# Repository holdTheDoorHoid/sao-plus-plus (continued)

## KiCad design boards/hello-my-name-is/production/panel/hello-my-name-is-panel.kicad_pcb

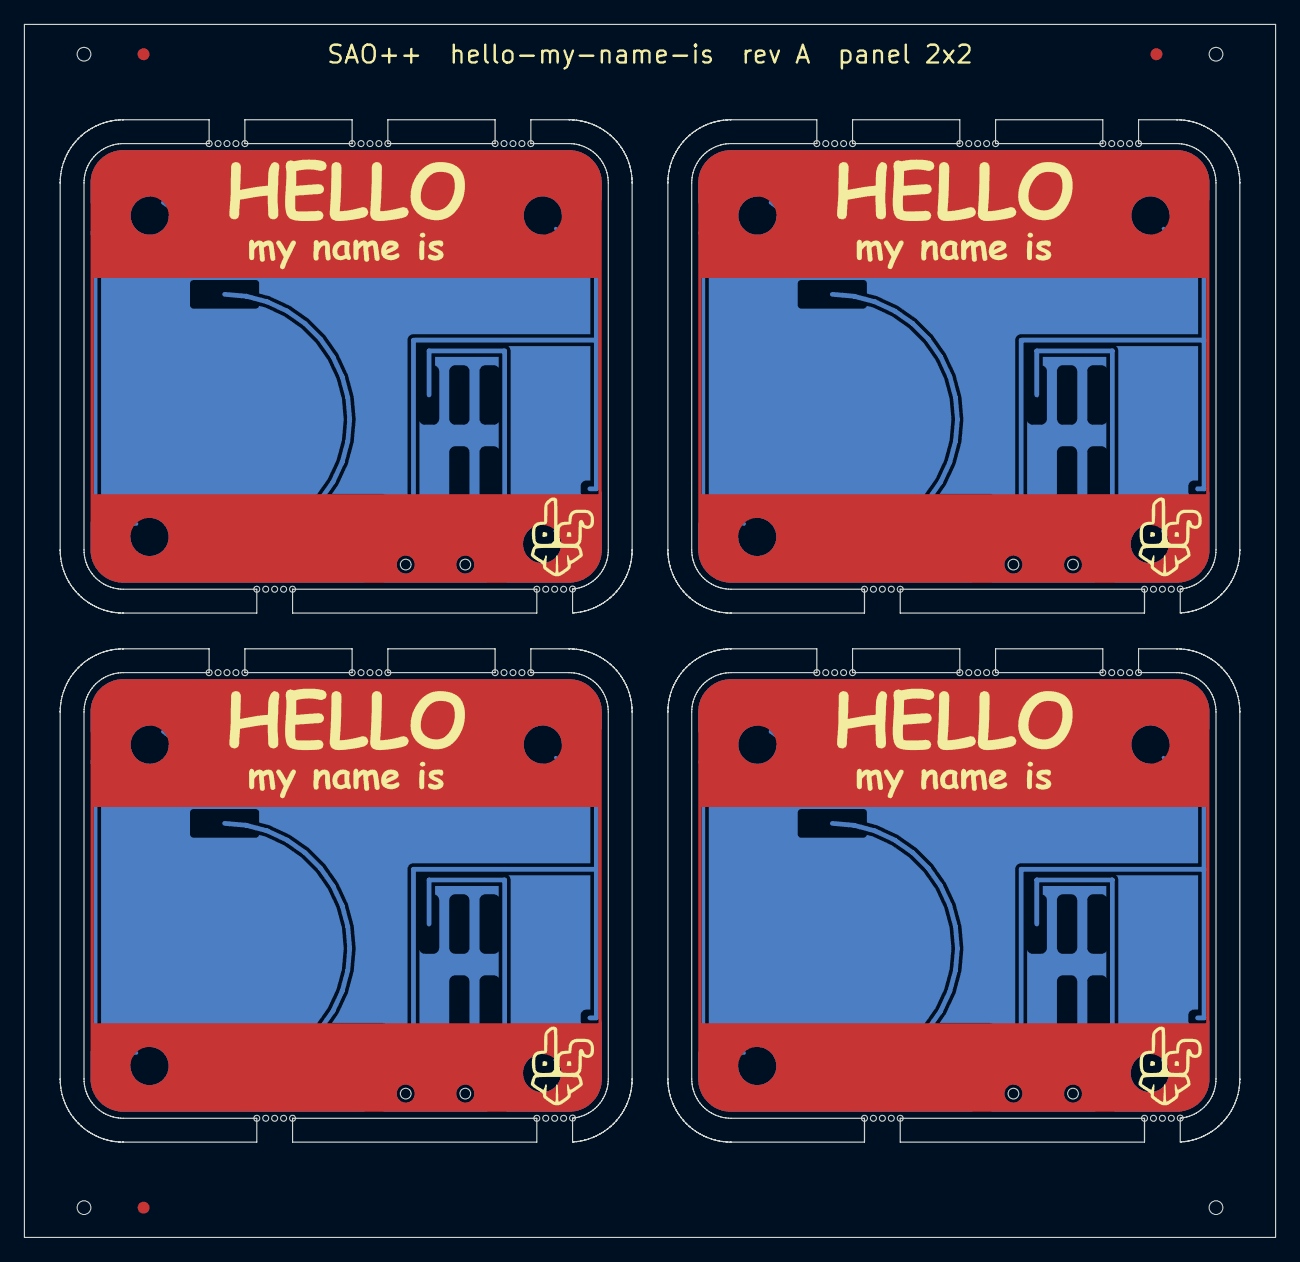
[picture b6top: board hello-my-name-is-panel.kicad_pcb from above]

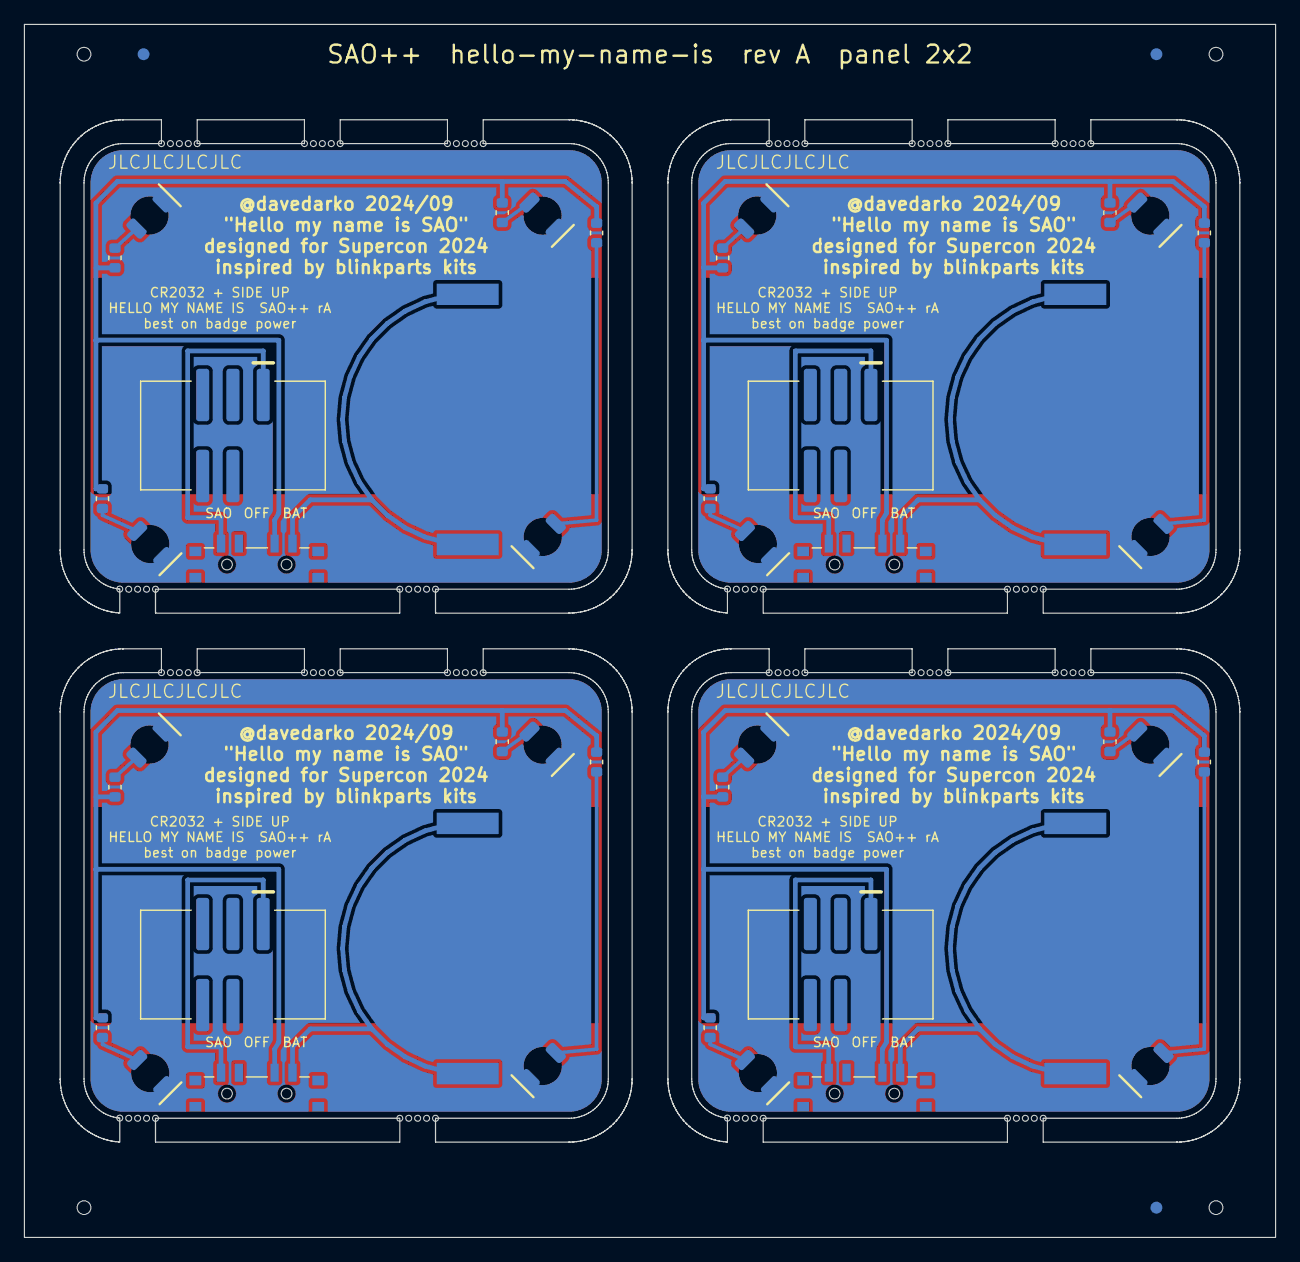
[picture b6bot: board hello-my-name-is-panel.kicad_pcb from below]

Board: 2 copper layers, 105.0 x 101.8 mm, 44 parts (44 on the bottom side), 32 nets.

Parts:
BT101, BT201, BT301, BT401: CR2032; SAOPP_BAT-01_CR2032_SMD_TE_BAT-HLD-001
D101, D102, D103, D104, D201, D202, D203, D204, D301, D302, D303, D304, D401, D402, D403, D404: white; SAOPP_LED-10_1206_ReverseMount_ThroughBoard
J101, J201, J301, J401: SAO v1.69bis; SAOPP_CONN-01_BoxHeader_2x03_P2.54mm_SMD_XFCN_BH254VS-6P
R101, R102, R103, R104, R201, R202, R203, R204, R301, R302, R303, R304, R401, R402, R403, R404: 1.3k; SAOPP_R_0603_1608Metric
SW101, SW201, SW301, SW401: SAO / OFF / BAT; SAOPP_SW-01_Slide_SP3T_CK_PCM13SMTR

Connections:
B2-GND: BT201.2, D201.1, D202.1, D203.1, D204.1, J201.2
B2-LED1_A: D201.2, R201.2
B2-LED2_A: D202.2, R202.2
B2-LED3_A: D203.2, R203.2
B2-LED4_A: D204.2, R204.2
B2-VBAT: BT201.1, SW201.4
B2-VLOAD: R201.1, R202.1, R203.1, R204.1, SW201.3
B2-VSAO: J201.1, SW201.1
B3-GND: BT301.2, D301.1, D302.1, D303.1, D304.1, J301.2
B3-LED1_A: D301.2, R301.2
B3-LED2_A: D302.2, R302.2
B3-LED3_A: D303.2, R303.2
B3-LED4_A: D304.2, R304.2
B3-VBAT: BT301.1, SW301.4
B3-VLOAD: R301.1, R302.1, R303.1, R304.1, SW301.3
B3-VSAO: J301.1, SW301.1
B4-GND: BT401.2, D401.1, D402.1, D403.1, D404.1, J401.2
B4-LED1_A: D401.2, R401.2
B4-LED2_A: D402.2, R402.2
B4-LED3_A: D403.2, R403.2
B4-LED4_A: D404.2, R404.2
B4-VBAT: BT401.1, SW401.4
B4-VLOAD: R401.1, R402.1, R403.1, R404.1, SW401.3
B4-VSAO: J401.1, SW401.1
GND: BT101.2, D101.1, D102.1, D103.1, D104.1, J101.2
LED1_A: D101.2, R101.2
LED2_A: D102.2, R102.2
LED3_A: D103.2, R103.2
LED4_A: D104.2, R104.2
VBAT: BT101.1, SW101.4
VLOAD: R101.1, R102.1, R103.1, R104.1, SW101.3
VSAO: J101.1, SW101.1

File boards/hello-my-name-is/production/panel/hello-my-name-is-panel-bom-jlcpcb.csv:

Comment,Designator,Footprint,LCSC Part #
CR2032,"BT101,BT201,BT301,BT401",SAOPP_BAT-01_CR2032_SMD_TE_BAT-HLD-001,C7501066
white,"D101,D102,D103,D104,D201,D202,D203,D204,D301,D302,D303,D304,D401,D402,D403,D404",SAOPP_LED-10_1206_ReverseMount_ThroughBoard,C575513
SAO v1.69bis,"J101,J201,J301,J401",SAOPP_CONN-01_BoxHeader_2x03_P2.54mm_SMD_XFCN_BH254VS-6P,C492445
1.3k,"R101,R102,R103,R104,R201,R202,R203,R204,R301,R302,R303,R304,R401,R402,R403,R404",SAOPP_R_0603_1608Metric,C22767
SAO / OFF / BAT,"SW101,SW201,SW301,SW401",SAOPP_SW-01_Slide_SP3T_CK_PCM13SMTR,C221842

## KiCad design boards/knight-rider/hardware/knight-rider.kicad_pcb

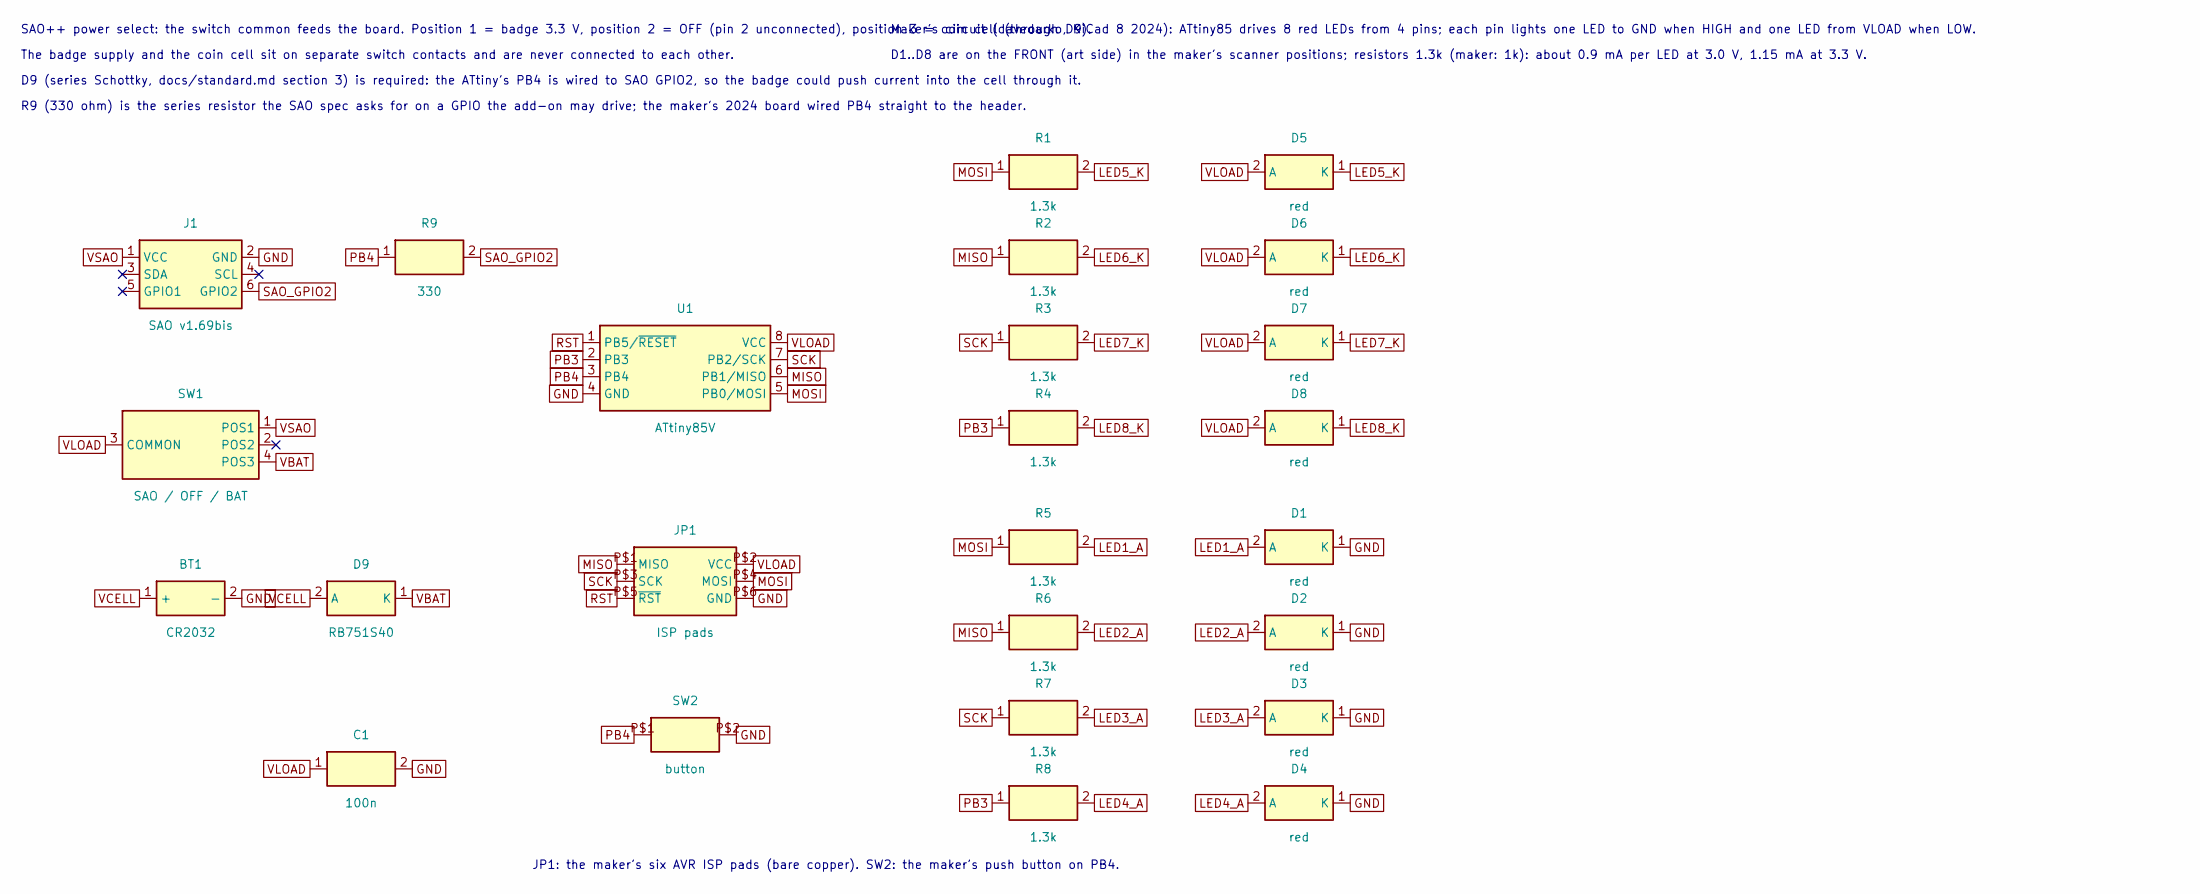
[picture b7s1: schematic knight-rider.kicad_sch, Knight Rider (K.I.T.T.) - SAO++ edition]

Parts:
BT1: CR2032; SAOPP_BAT-01_CR2032_SMD_TE_BAT-HLD-001; MPN BAT-HLD-001; LCSC C7501066
C1: 100n; SAOPP_C_0603_1608Metric; MPN CC0603KRX7R9BB104; LCSC C14663
D1, D2, D3, D4, D5, D6, D7, D8: red; LED_0603_1608Metric_Pad1.05x0.95mm_HandSolder; MPN LTST-C191KRKT; LCSC C125099
D9: RB751S40; D_SOD-523; MPN RB751S40T1G; LCSC C232576
J1: SAO v1.69bis; SAOPP_CONN-01_BoxHeader_2x03_P2.54mm_SMD_XFCN_BH254VS-6P; MPN BH254VS-6P; LCSC C492445
JP1: ISP pads; 2X3_SMD_PAD; MPN none: bare pads, nothing fitted
R1, R2, R3, R4, R5, R6, R7, R8: 1.3k; SAOPP_R_0603_1608Metric; MPN 0603WAF1301T5E; LCSC C22767
R9: 330; SAOPP_R_0603_1608Metric; MPN 0603WAF3300T5E; LCSC C23138
SW1: SAO / OFF / BAT; SAOPP_SW-01_Slide_SP3T_CK_PCM13SMTR; MPN PCM13SMTR; LCSC C221842
SW2: button; TACTILE-SWITCH-1101NE; MPN SparkFun COM-08229 class (6 x 3.5 mm, 2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
U1: ATtiny85V; SO08-EIAJ; MPN ATTINY85V-10SU; LCSC C152192

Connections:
GND: BT1.2 (-), C1.2, D1.1 (K), D2.1 (K), D3.1 (K), D4.1 (K), J1.2 (GND), JP1.P$6 (GND), SW2.P$2, U1.4 (GND)
LED1_A: D1.2 (A), R5.2
LED2_A: D2.2 (A), R6.2
LED3_A: D3.2 (A), R7.2
LED4_A: D4.2 (A), R8.2
LED5_K: D5.1 (K), R1.2
LED6_K: D6.1 (K), R2.2
LED7_K: D7.1 (K), R3.2
LED8_K: D8.1 (K), R4.2
MISO: JP1.P$1 (MISO), R2.1, R6.1, U1.6 (PB1/MISO)
MOSI: JP1.P$4 (MOSI), R1.1, R5.1, U1.5 (PB0/MOSI)
PB3: R4.1, R8.1, U1.2 (PB3)
PB4: R9.1, SW2.P$1, U1.3 (PB4)
RST: JP1.P$5 (~RST), U1.1 (PB5/~RESET)
SAO_GPIO2: J1.6 (GPIO2), R9.2
SCK: JP1.P$3 (SCK), R3.1, R7.1, U1.7 (PB2/SCK)
VBAT: D9.1 (K), SW1.4 (POS3)
VCELL: BT1.1 (+), D9.2 (A)
VLOAD: C1.1, D5.2 (A), D6.2 (A), D7.2 (A), D8.2 (A), JP1.P$2 (VCC), SW1.3 (COMMON), U1.8 (VCC)
VSAO: J1.1 (VCC), SW1.1 (POS1)

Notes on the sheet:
SAO++ power select: the switch common feeds the board. Position 1 = badge 3.3 V, position 2 = OFF (pin 2 unconnected), position 3 = coin cell (through D9).
The badge supply and the coin cell sit on separate switch contacts and are never connected to each other.
D9 (series Schottky, docs/standard.md section 3) is required: the ATtiny's PB4 is wired to SAO GPIO2, so the badge could push current into the cell through it.
R9 (330 ohm) is the series resistor the SAO spec asks for on a GPIO the add-on may drive; the maker's 2024 board wired PB4 straight to the header.
Maker's circuit (davedarko, KiCad 8 2024): ATtiny85 drives 8 red LEDs from 4 pins; each pin lights one LED to GND when HIGH and one LED from VLOAD when LOW.
D1..D8 are on the FRONT (art side) in the maker's scanner positions; resistors 1.3k (maker: 1k): about 0.9 mA per LED at 3.0 V, 1.15 mA at 3.3 V.
JP1: the maker's six AVR ISP pads (bare copper). SW2: the maker's push button on PB4.

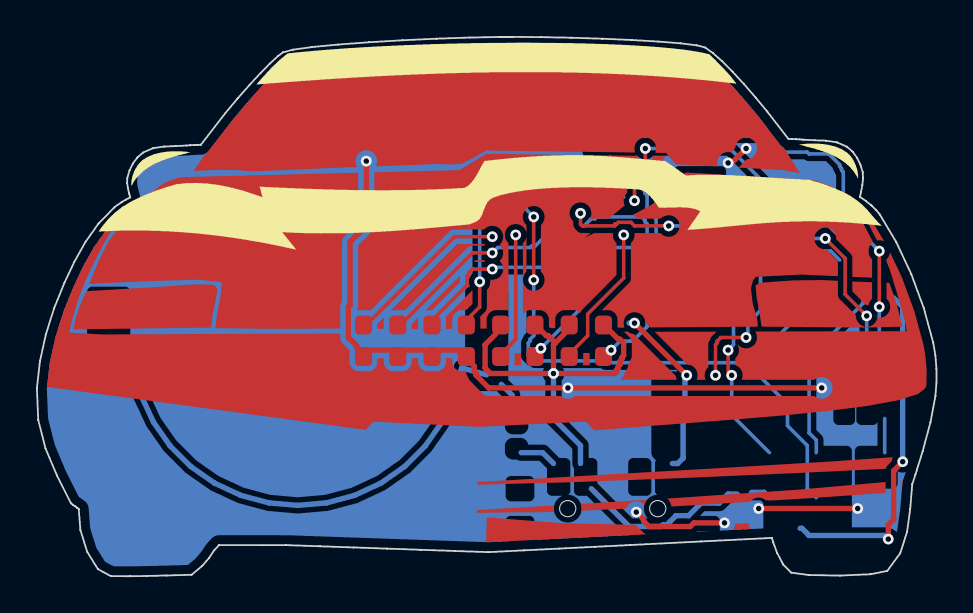
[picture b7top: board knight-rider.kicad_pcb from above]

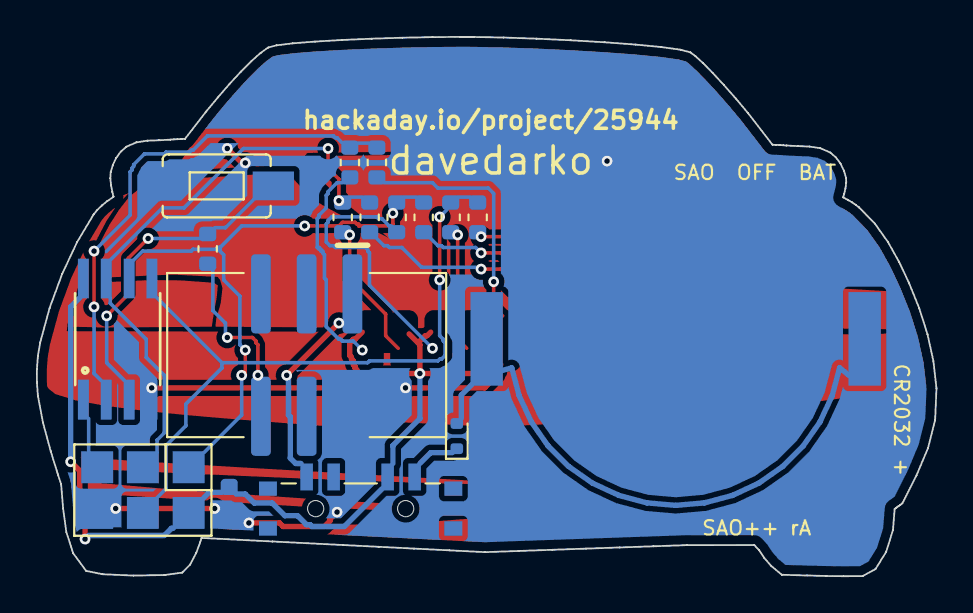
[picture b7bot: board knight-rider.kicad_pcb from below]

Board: 2 copper layers, 50.0 x 30.0 mm, 25 parts (17 on the bottom side), 20 nets.

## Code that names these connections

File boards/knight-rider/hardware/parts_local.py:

"""Parts Knight Rider needs that the shared SAO++ library does not have (yet). Read by tools/saopp_symbols.load_local.

Format as in tools/saopp_symbols.py:
  name: (ref prefix, value, footprint, fields, half-width, [(pin number, pin name, side, row), ...])
Land patterns: the maker's own 2024 KiCad 8 footprints (ATtiny, ISP pads, button, front LED) and KiCad's stock SOD-523
(diode), copied into knight-rider-local.pretty by make_local_footprints.py. LCSC numbers are left for the orchestrator.
"""
LOCAL_SYMBOLS = {
    # the maker's chip: ATtiny85 in the 208 mil (EIAJ) SOIC-8. The low-voltage "V" grade (1.8-5.5 V) because on the coin
    # cell the chip sees about 2.7 V after the cell diode, which is the bottom of the standard -20 grade's range
    "ATtiny85_SOIC8_EIAJ": ("U", "ATtiny85V", "knight-rider-local:SO08-EIAJ",
                            {"SAOPP_ID": "", "MPN": "ATTINY85V-10SU", "LCSC": "C152192"}, 5,
                            [("1", "PB5/~{RESET}", "L", 0), ("2", "PB3", "L", 1), ("3", "PB4", "L", 2), ("4", "GND", "L", 3),
                             ("8", "VCC", "R", 0), ("7", "PB2/SCK", "R", 1), ("6", "PB1/MISO", "R", 2), ("5", "PB0/MOSI", "R", 3)]),
    # forward-facing red LED for the scanner, on the FRONT (art side) where the maker had it
    "LED_0603_Red_Front": ("D", "red", "knight-rider-local:LED_0603_1608Metric_Pad1.05x0.95mm_HandSolder",
                           {"SAOPP_ID": "", "MPN": "LTST-C191KRKT", "LCSC": "C125099"}, 2,
                           [("2", "A", "L", 0), ("1", "K", "R", 0)]),
    # the maker's push button (pattern mode); 6 x 3.5 mm two-pad SMD tactile switch
    "Button_SMD_6x3.5": ("SW", "button", "knight-rider-local:TACTILE-SWITCH-1101NE",
                         {"SAOPP_ID": "", "MPN": "SparkFun COM-08229 class (6 x 3.5 mm, 2 pads at 6.3 mm)", "LCSC": ""}, 2,
                         [("P$1", "~", "L", 0), ("P$2", "~", "R", 0)]),
    # the maker's six AVR ISP programming pads (bare copper, nothing fitted); standard AVR 6-pin ISP order
    "ISP_Pads_AVR_2x3": ("JP", "ISP pads", "knight-rider-local:2X3_SMD_PAD",
                         {"SAOPP_ID": "", "MPN": "none: bare pads, nothing fitted", "LCSC": ""}, 3,
                         [("P$1", "MISO", "L", 0), ("P$3", "SCK", "L", 1), ("P$5", "~{RST}", "L", 2),
                          ("P$2", "VCC", "R", 0), ("P$4", "MOSI", "R", 1), ("P$6", "GND", "R", 2)]),
    # the series cell diode docs/standard.md section 3 requires (this board wires the ATtiny to SAO GPIO2)
    "D_Schottky_Cell": ("D", "RB751S40", "knight-rider-local:D_SOD-523",
                        {"SAOPP_ID": "SAOPP-D-01", "MPN": "RB751S40T1G", "LCSC": "C232576"}, 2,
                        [("2", "A", "L", 0), ("1", "K", "R", 0)]),
}

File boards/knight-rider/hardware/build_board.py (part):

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ISP = (167.6, 115.2)
isp = place("JP1", ISP, ("P$1", (ISP[0] - 2.54, ISP[1] - 1.27)))   # top row MISO SCK RST, bottom row VCC MOSI GND
BTN = (163.5, 98.3)
btn = place("SW2", BTN, ("P$1", (BTN[0] - 3.15, BTN[1])))          # PB4 pad on the left
C1_C = (162.8, 115.8)
c1 = place("C1", C1_C, ("1", (C1_C[0], C1_C[1] - 0.825)))
D9_C = (150.16, 112.2)
d9 = place("D9", D9_C, ("2", (D9_C[0], D9_C[1] - 0.7)))             # anode (cell side) up
R9_C = (164.0, 101.8)
res = {"R9": place("R9", R9_C, ("1", (R9_C[0], R9_C[1] - 0.825)))}   # vertical: PB4 up, badge GPIO2 down

RX = [149.0 + 1.5 * k for k in range(6)]       # resistor row between the "davedarko" line and the connector
R_SLOTS = {}
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
POWER = {"VLOAD": 0.3, "VSAO": 0.3, "VBAT": 0.3, "VCELL": 0.3, "GND": 0.3}
ORDER = [f"LED{k}_A" for k in range(4, 0, -1)] + [f"LED{k}_K" for k in range(5, 9)] + \
        ["MOSI", "MISO", "SCK", "PB3", "RST", "PB4", "SAO_GPIO2", "VSAO", "VBAT", "VCELL", "VLOAD", "GND"]
ROUTE_FAIL = []
for net in ORDER:
    tg = [(L, g.poly_mask(ps, 0)) for ref, num, n, L, ps in PADS if n == net and not (ref == "BT1" and num == "2")
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
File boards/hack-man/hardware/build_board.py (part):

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j = {n: pp(conn, n) for n in "123456"}
route("VSAO", [(j["1"][0] - 0.3, j["1"][1] + 0.7), (135.0, j["1"][1] + 0.7), (s1[0], j["1"][1] + 4.7), s1], PWR)

# SAO GPIO1 -> 330R -> D7, along the top
route("SAO_GPIO1", [(j["5"][0] + 0.3, R2_C[1]), pp(r2, "1")])
route("D7_RX", [pp(r2, "2"), (d7[0] - 4.4, R2_C[1]), (d7[0] - 2.9, d7[1]), d7])

# under the LiPo connector: four tracks pass between its signal pads and its hold-down pads
T0 = JST[1] - 1.1 + 0.45
LANE = [T0, T0 + 0.45, T0 + 0.9, T0 + 1.35]                     # SDA, SCL, GPIO2, OFF sense
d4, d5, d6, d1 = pp(xiao, "5"), pp(xiao, "6"), pp(xiao, "7"), pp(xiao, "2")
GAP_Y = (CONN[1] - 0.4, CONN[1] + 0.4)                          # between the connector's two pad rows
route("SDA", [j["3"], (j["3"][0], GAP_Y[0]), (160.5, GAP_Y[0]), (160.5, LANE[0]), (d4[0], LANE[0]), d4])
route("SCL", [j["4"], (j["4"][0], GAP_Y[1]), (159.9, GAP_Y[1]), (159.9, LANE[1]), (d5[0], LANE[1]), d5])
route("SAO_GPIO2", [(j["6"][0] + 0.3, R3_C[1]), pp(r3, "1")])
JR = JST[0] + 4.1                                               # right edge of the connector's right hold-down pad
route("D6_TX", [pp(r3, "2"), (159.3, R3_C[1]), (159.3, LANE[2]), (JR + 1.2, LANE[2]), (JR + 1.2, d6[1]), d6])

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
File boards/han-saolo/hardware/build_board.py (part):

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  - loads original/SoloCarbonite/SoloCarbonite.kicad_pcb so the front art (copper, mask, silk) stays exactly as drawn
  - removes every old part, track, via and zone; the front copper is put back as fixed shapes cut from the maker's own
    zone fills (so it looks exactly as he made it), minus the two new switch peg holes
  - keeps the maker's circuit: ATtiny412 driving five SK6805-EC3210R side-firing RGB LEDs from PA6, with the maker's
    LED-data jumper. New: the shared SMD SAO connector, the SAO / OFF / BAT switch, the CR2032 clip, the series cell
    diode, a UPDI programming pad
  - places everything on the back and routes it on the back copper; the back copper is the GND net, 0.55 mm clear of
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# ---- footprints -----------------------------------------------------------------------------------------------------
conn = place("J1", CONN, ("1", (CONN[0] - 2.54, CONN[1] - 3.4)))     # VCC top-left in front view (as Mad Cat), key slot up
sw = place("SW1", SW, ("4", (SW[0] + 1.43, SW[1] - 3.0)))           # pins face the board, pin 4 (BAT) on top
u1 = place("U1", U1C, ("1", (U1C[0] + 2.475, U1C[1] - 1.905)))      # pin 1 top-right: VCC up, SDA/SCL down, PA6 right
led = {}
for ref, ((x, y), s) in LEDS.items():
    ox = x + s * LED_LENS_X
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D6C = (2.0, 29.6)
d6 = place("D6", D6C, ("2", (D6C[0] + 0.7, D6C[1])))                # above the clip (clear of its courtyard): anode right
JP1C = (17.9, 50.95)
jp1 = place("JP1", JP1C, ("1", (JP1C[0], JP1C[1] - 1.3)))           # pad 1 (PA6) on top, 2 = LED data, 3 (GPIO1) below
TP2C = (6.2, 52.0)
tp2 = place("TP2", TP2C, ("1", TP2C))
tp1 = place("TP1", (12.49, 14.12), ("1", (12.49, 14.12)))           # the maker's chain-out pad, where he had it
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route("VLOAD", [(TRUNK_X, L["D5"]["4"][1]), L["D5"]["4"]], 0.3)                              # D5 (the face)
route("VLOAD", [u["1"], (u["1"][0], V_Y)], 0.3)                                              # ATtiny VCC

# LED data: PA6 -> jumper -> D1 -> up the right edge -> D2 -> D3 -> D4 -> across the top -> D5 (face) -> TP1
jpp = {n: pp(jp1, n) for n in "123"}
route("NEO_PA6", [u["2"], (15.4, u["2"][1]), (15.94, jpp["1"][1]), jpp["1"]])
route("LED_DIN", [jpp["2"], (19.0, jpp["2"][1]), (19.15, L["D1"]["3"][1]), L["D1"]["3"]])
route("SAO_GPIO1", [(j["5"][0], j["5"][1] - 2.0), jpp["3"]])
d1o = L["D1"]["2"]
route("LED_D1", [d1o, (22.3, d1o[1] - 0.6), (CORR_D, d1o[1] - 0.6 - (CORR_D - 22.3)), (CORR_D, 27.1), (22.35, 27.1),
                 (22.35, L["D2"]["3"][1] + 0.6), L["D2"]["3"]])
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
print("[0]", "back silkscreen ---", round(time.time() - _T0, 1), flush=True)
# ---- back silkscreen ------------------------------------------------------------------------------------------------
# the maker's jumper legend (PA6 / NEO / SWT and PA0 / RST / IO2) sat where the switch now is. It moves, words, letter
# size and layout unchanged, to the free space between "Really? ..." and the top of the cell (the only gap it fits)
legend = [t for t in board.GetDrawings() if t.GetLayer() == B_SilkS and isinstance(t, pcbnew.PCB_TEXT)
          and t.GetText().split("\n")[0] in ("PA6", "NEO", "PA0")]
assert len(legend) == 3, [t.GetText() for t in legend]
lb = pcbnew.BOX2I()
for t in legend:
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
